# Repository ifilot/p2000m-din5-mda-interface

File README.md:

# P2000M DIN5 to MDA

PCB that translates the DIN5 video output of the P2000M to a MDA-compatible
female socket. Several testpoints are added to attach oscilloscope probes.

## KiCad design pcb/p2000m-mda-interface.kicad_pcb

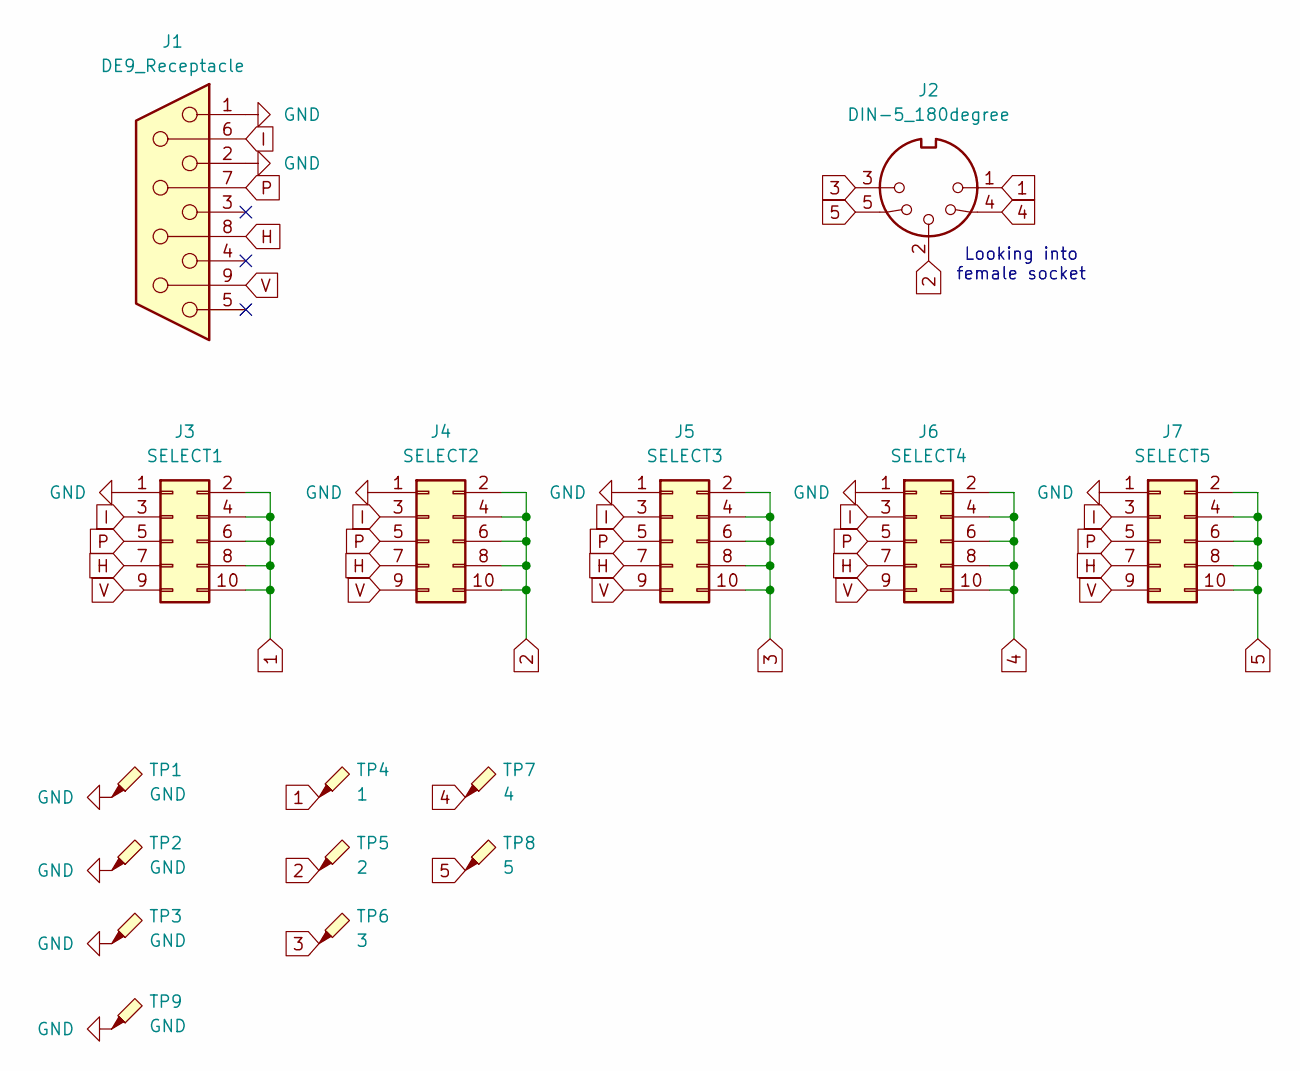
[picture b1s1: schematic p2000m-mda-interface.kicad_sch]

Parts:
J1: DE9_Receptacle; DSUB-9_Male_Horizontal_P2.77x2.84mm_EdgePinOffset4.94mm_Hou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
J2: DIN-5_180degree; DIN5
J3: SELECT1; PinHeader_2x05_P2.54mm_Vertical
J4: SELECT2; PinHeader_2x05_P2.54mm_Vertical
J5: SELECT3; PinHeader_2x05_P2.54mm_Vertical
J6: SELECT4; PinHeader_2x05_P2.54mm_Vertical
J7: SELECT5; PinHeader_2x05_P2.54mm_Vertical
TP1, TP2, TP3, TP9: GND; TestPoint_Bridge_Pitch2.54mm_Drill1.0mm
TP4: 1; TestPoint_Bridge_Pitch2.54mm_Drill1.0mm
TP5: 2; TestPoint_Bridge_Pitch2.54mm_Drill1.0mm
TP6: 3; TestPoint_Bridge_Pitch2.54mm_Drill1.0mm
TP7: 4; TestPoint_Bridge_Pitch2.54mm_Drill1.0mm
TP8: 5; TestPoint_Bridge_Pitch2.54mm_Drill1.0mm

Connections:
1: J2.1, J3.2, J3.4, J3.6, J3.8, J3.10, TP4.1
2: J2.2, J4.2, J4.4, J4.6, J4.8, J4.10, TP5.1
3: J2.3, J5.2, J5.4, J5.6, J5.8, J5.10, TP6.1
4: J2.4, J6.2, J6.4, J6.6, J6.8, J6.10, TP7.1
5: J2.5, J7.2, J7.4, J7.6, J7.8, J7.10, TP8.1
GND: J1.1, J1.2, J3.1, J4.1, J5.1, J6.1, J7.1, TP1.1, TP2.1, TP3.1, TP9.1
H: J1.8, J3.7, J4.7, J5.7, J6.7, J7.7
I: J1.6, J3.3, J4.3, J5.3, J6.3, J7.3
P: J1.7, J3.5, J4.5, J5.5, J6.5, J7.5
V: J1.9, J3.9, J4.9, J5.9, J6.9, J7.9

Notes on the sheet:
Looking into female socket

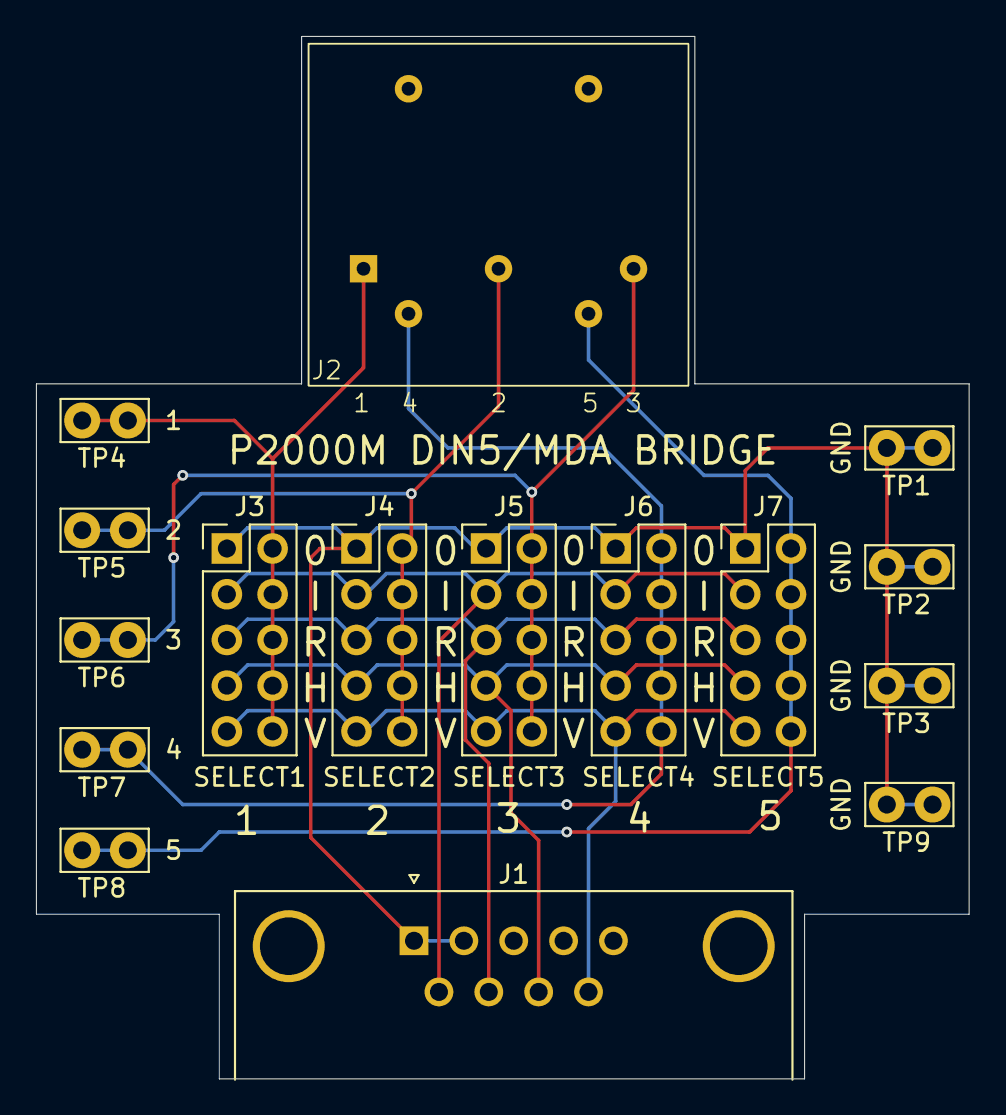
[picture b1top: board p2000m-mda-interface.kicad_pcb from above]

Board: 2 copper layers, 51.8 x 57.9 mm, 16 parts (0 on the bottom side), 10 nets.
